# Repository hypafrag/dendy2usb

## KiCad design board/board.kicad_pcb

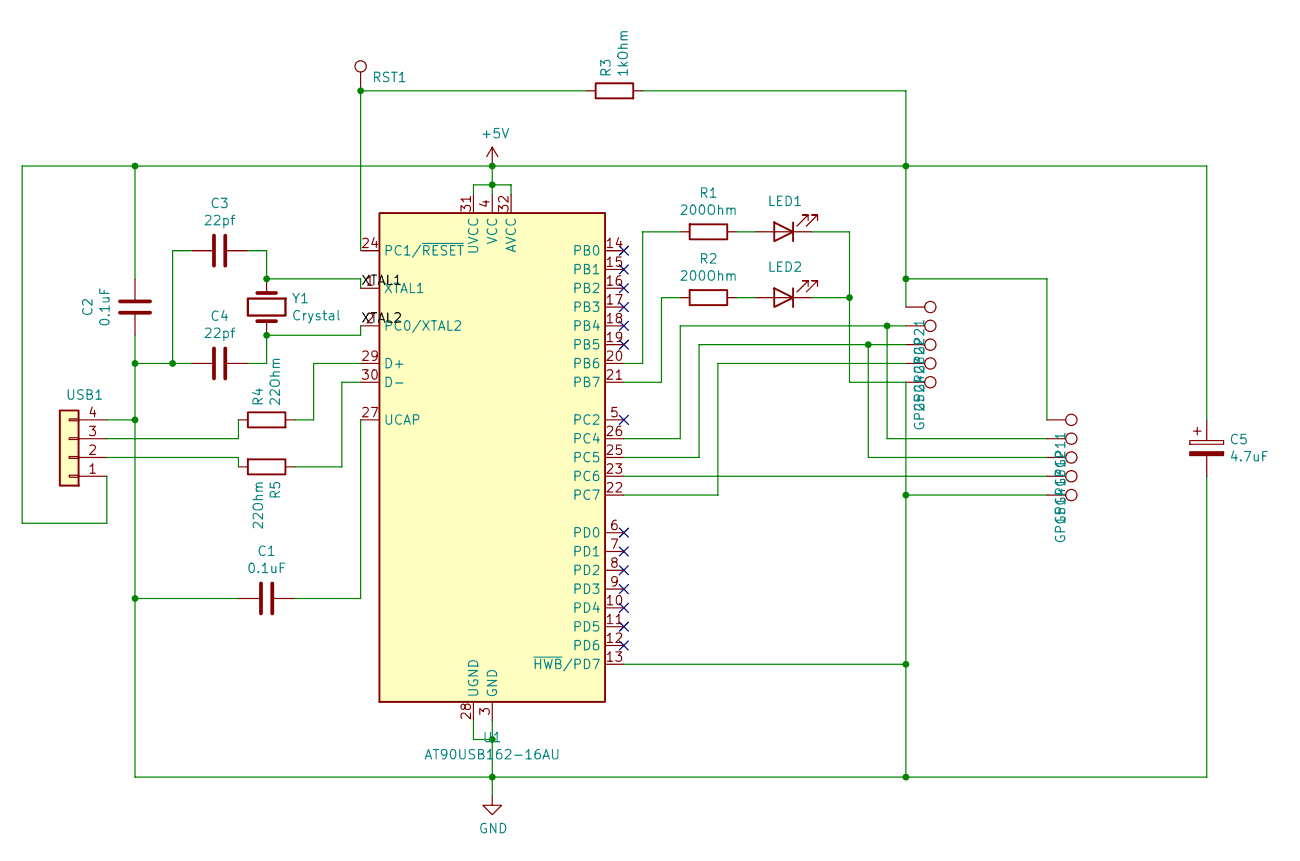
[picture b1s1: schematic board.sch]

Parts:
C1, C2: 0.1uF; C_0805_2012Metric
C3, C4: 22pf; C_0805_2012Metric
C5: 4.7uF; C_Radial_D5.0mm_H5.0mm_P2.00mm
GP11, GP12, GP13, GP14, GP15, GP21, GP22, GP23, GP24, GP25: TestPoint; TestPoint_Pad_2.0x2.0mm
LED1, LED2: LED; LED_0201_0603Metric
R1, R2: 200Ohm; R_0805_2012Metric
R3: 1kOhm; R_0805_2012Metric
R4, R5: 22Ohm; R_0805_2012Metric
RST1: TestPoint; TestPoint_Pad_2.0x2.0mm
U1: AT90USB162-16AU; TQFP-32_7x7mm_P0.8mm
USB1: Conn_01x04; PinHeader_1x04_P2.54mm_Vertical
Y1: Crystal; Crystal_SMD_HC49-SD

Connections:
+5V: C2.1, C5.1, GP11.1, GP21.1, R3.2, U1.4 (VCC), U1.31 (UVCC), U1.32 (AVCC), USB1.1
/XTAL1: C3.1, U1.1 (XTAL1), Y1.1
/XTAL2: C4.2, U1.2 (PC0/XTAL2), Y1.2
GND: C1.2, C2.2, C3.2, C4.1, C5.2, GP15.1, GP25.1, LED1.1 (K), LED2.1 (K), U1.3 (GND), U1.13 (~HWB~/PD7), U1.28 (UGND), USB1.4
unnamed: C1.1, U1.27 (UCAP)
unnamed: GP12.1, GP22.1, U1.26 (PC4)
unnamed: GP13.1, GP23.1, U1.25 (PC5)
unnamed: GP14.1, U1.23 (PC6)
unnamed: GP24.1, U1.22 (PC7)
unnamed: LED1.2 (A), R1.1
unnamed: LED2.2 (A), R2.1
unnamed: R1.2, U1.20 (PB6)
unnamed: R2.2, U1.21 (PB7)
unnamed: R3.1, RST1.1, U1.24 (PC1/~RESET)
unnamed: R4.1, USB1.3
unnamed: R4.2, U1.29 (D+)
unnamed: R5.1, U1.30 (D-)
unnamed: R5.2, USB1.2

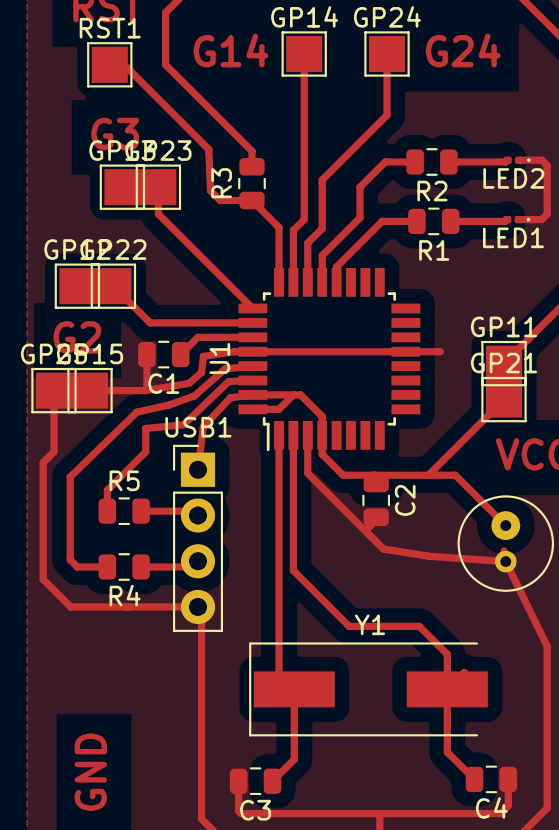
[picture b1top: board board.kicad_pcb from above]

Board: 2 copper layers, 26 parts (0 on the bottom side), 18 nets.

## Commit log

2020-09-19 init
2020-09-19 building
